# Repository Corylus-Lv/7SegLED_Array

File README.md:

# 7SegLED_Array

7セグメントLED表示ブロックに使用するPCBの設計データです。

**Still under construction**  

CC BY-NC-SA 3.0

**免責事項：**  
このプロジェクトに掲載した情報については「現状のまま」で、明示であるか暗黙であるかを問わず、何らの保証もありません。
この情報の利用またはその他の扱いに関連した、請求、損害、その他の義務については一切の責任を負うものではありません。

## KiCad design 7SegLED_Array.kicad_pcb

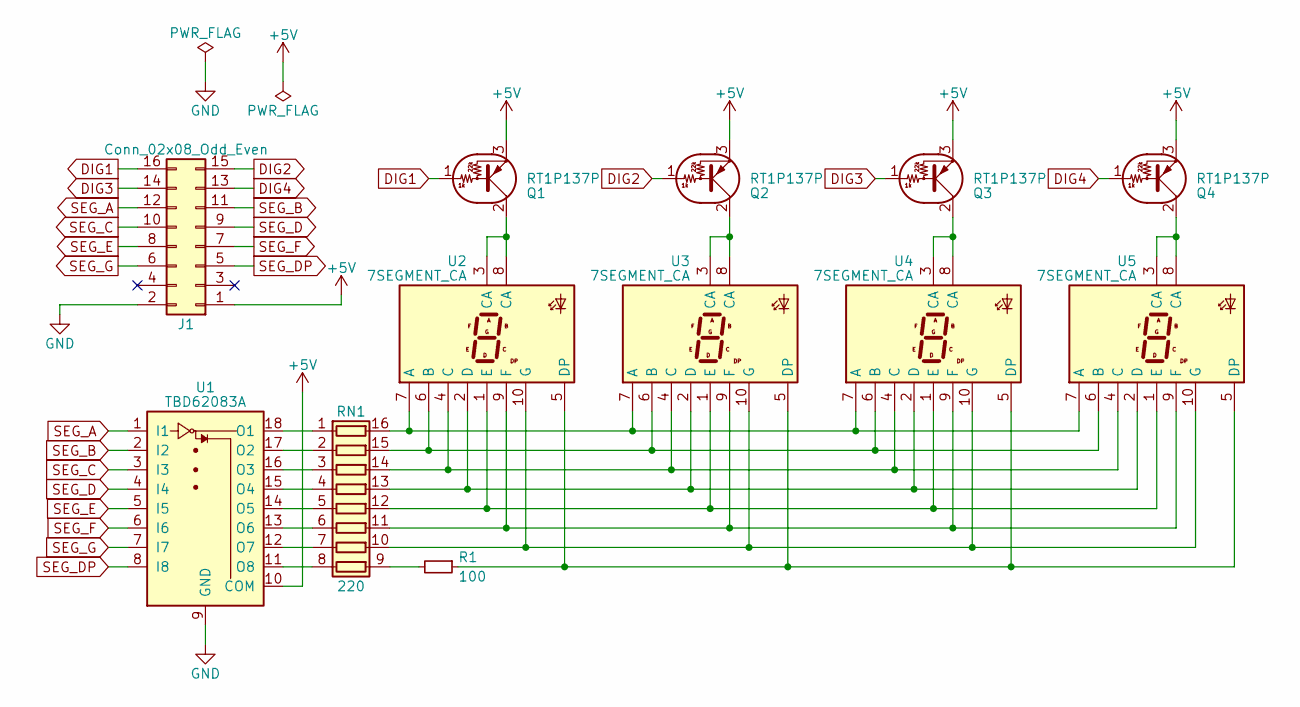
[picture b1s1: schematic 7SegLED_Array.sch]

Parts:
J1: Conn_02x08_Odd_Even; Pin_Header_Angled_2x08_Pitch2.54mm
Q1, Q2, Q3, Q4: RT1P137P; SOT-89-3_Handsoldering
R1: 100; R_0603_HandSoldering
RN1: 220; R_Array_Convex_8x0602
U1: TBD62083A; DIP-18_W7.62mm_LongPads
U2, U3, U4, U5: 7SEGMENT_CA; 7SegmentLED_LTS6760_LTS6780

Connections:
+5V: J1.1, Q1.3 (E), Q2.3 (E), Q3.3 (E), Q4.3 (E), U1.10 (COM)
DIG1: J1.16, Q1.1 (B)
DIG2: J1.15, Q2.1 (B)
DIG3: J1.14, Q3.1 (B)
DIG4: J1.13, Q4.1 (B)
GND: J1.2, U1.9 (GND)
unnamed: Q1.2 (C), U2.3 (CA), U2.8 (CA)
unnamed: Q2.2 (C), U3.3 (CA), U3.8 (CA)
unnamed: Q3.2 (C), U4.3 (CA), U4.8 (CA)
unnamed: Q4.2 (C), U5.3 (CA), U5.8 (CA)
unnamed: R1.1, U2.5 (DP), U3.5 (DP), U4.5 (DP), U5.5 (DP)
unnamed: R1.2, RN1.9 (R8.2)
unnamed: RN1.1 (R1.1), U1.18 (O1)
unnamed: RN1.2 (R2.1), U1.17 (O2)
unnamed: RN1.3 (R3.1), U1.16 (O3)
unnamed: RN1.4 (R4.1), U1.15 (O4)
unnamed: RN1.5 (R5.1), U1.14 (O5)
unnamed: RN1.6 (R6.1), U1.13 (O6)
unnamed: RN1.7 (R7.1), U1.12 (O7)
unnamed: RN1.8 (R8.1), U1.11 (O8)
unnamed: RN1.10 (R7.2), U2.10 (G), U3.10 (G), U4.10 (G), U5.10 (G)
unnamed: RN1.11 (R6.2), U2.9 (F), U3.9 (F), U4.9 (F), U5.9 (F)
unnamed: RN1.12 (R5.2), U2.1 (E), U3.1 (E), U4.1 (E), U5.1 (E)
unnamed: RN1.13 (R4.2), U2.2 (D), U3.2 (D), U4.2 (D), U5.2 (D)
unnamed: RN1.14 (R3.2), U2.4 (C), U3.4 (C), U4.4 (C), U5.4 (C)
unnamed: RN1.15 (R2.2), U2.6 (B), U3.6 (B), U4.6 (B), U5.6 (B)
unnamed: RN1.16 (R1.2), U2.7 (A), U3.7 (A), U4.7 (A), U5.7 (A)
SEG_A: J1.12, U1.1 (I1)
SEG_B: J1.11, U1.2 (I2)
SEG_C: J1.10, U1.3 (I3)
SEG_D: J1.9, U1.4 (I4)
SEG_DP: J1.5, U1.8 (I8)
SEG_E: J1.8, U1.5 (I5)
SEG_F: J1.7, U1.6 (I6)
SEG_G: J1.6, U1.7 (I7)

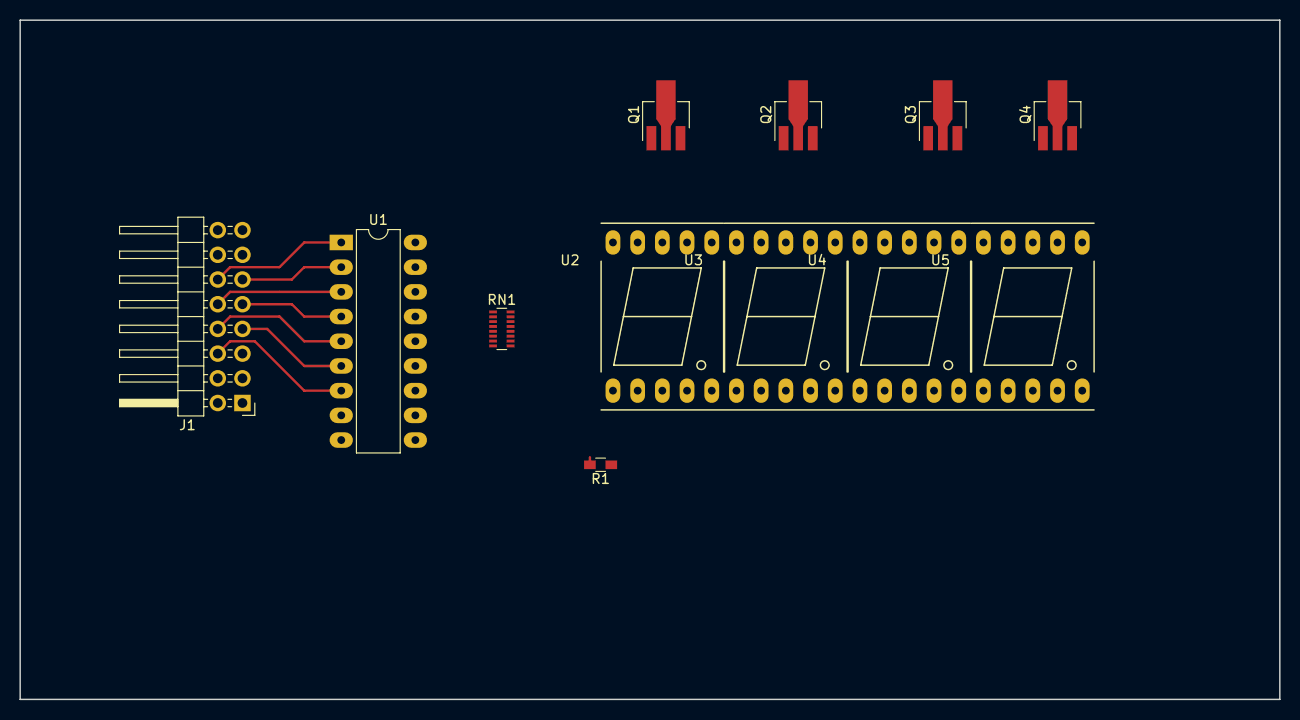
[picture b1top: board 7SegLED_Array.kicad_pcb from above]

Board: 2 copper layers, 129.5 x 69.9 mm, 12 parts (0 on the bottom side), 35 nets.

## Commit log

2018-08-29 KiCAD 5
2019-03-12 edit
